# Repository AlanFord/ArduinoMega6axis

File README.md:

# ArduinoMega6axis
A stepper motor control shield for an Arduino Mega that will support 3 primary off-board motor controllers and 3 on-board Pololu A4988 controllers.  This supports work done at Build,RVA (http://rvabuild.com) to construct a Robot Arm (see http://fablab.ruc.dk/robot-arm-v-0-1/ ).

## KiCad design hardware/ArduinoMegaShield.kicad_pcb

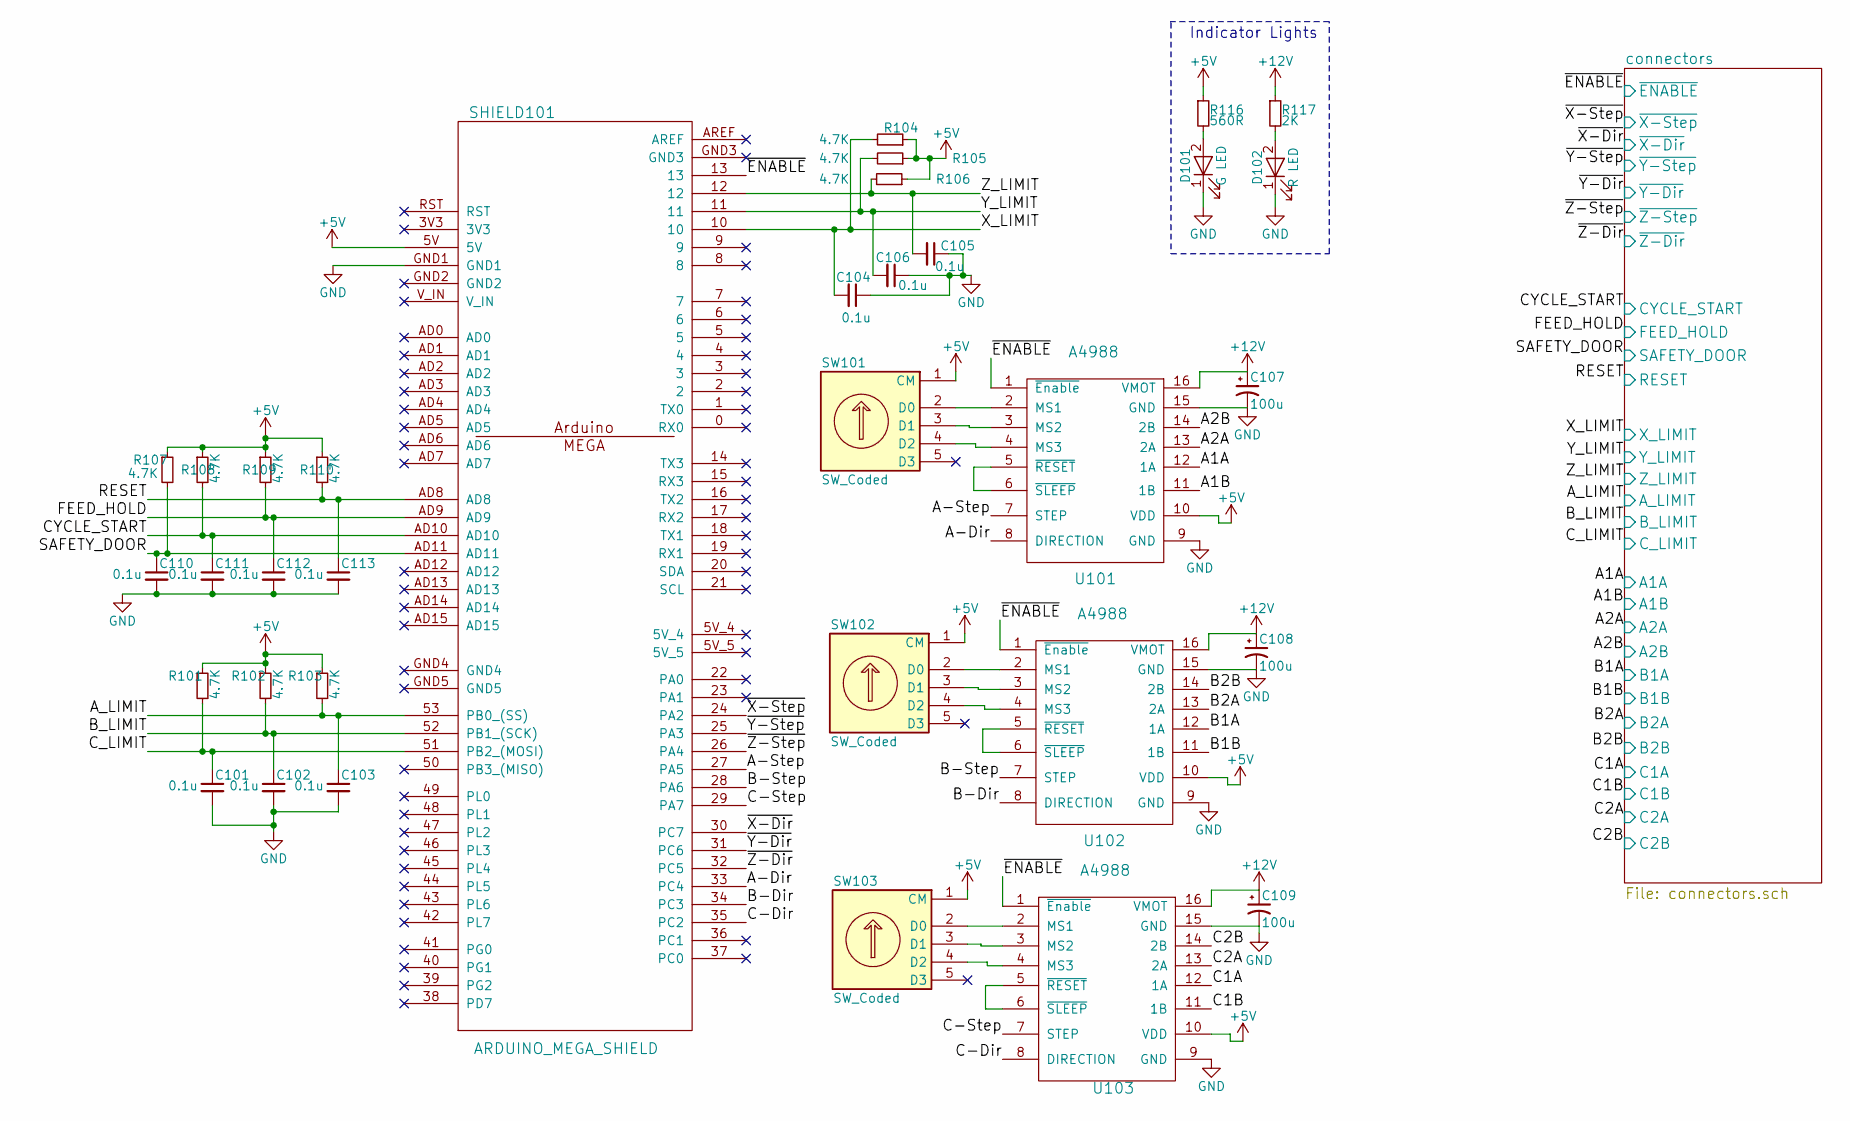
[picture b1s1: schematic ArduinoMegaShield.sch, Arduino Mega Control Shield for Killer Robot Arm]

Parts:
C101, C102, C103, C104, C105, C106, C110, C111, C112, C113: 0.1u; C_0805_HandSoldering
C107, C108, C109: 100u; C_Radial_D6.3_L11.2_P2.5; MPN EEU-FM1E101
D101: G LED; LED_0805
D102: R LED; LED_0805
R101, R102, R103, R104, R105, R106, R107, R108, R109, R110: 4.7K; R_0805_HandSoldering
R116: 560R; R_0805_HandSoldering
R117: 2K; R_0805_HandSoldering
SHIELD101: ARDUINO_MEGA_SHIELD
SW101, SW102, SW103: SW_Coded; S-1010A; MPN Copal S-1010A
U101, U102, U103: A4988

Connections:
+5V: R101.1, R102.1, R103.1, R104.1, R105.1, R106.1, R107.1, R108.1, R109.1, R110.1, R116.1, SHIELD101.5V, SW101.1 (CM), SW102.1 (CM), SW103.1 (CM), U101.10 (VDD), U102.10 (VDD), U103.10 (VDD); also elsewhere on the board
+12V: C107.1, C108.1, C109.1, R117.1, U101.16 (VMOT), U102.16 (VMOT), U103.16 (VMOT); also elsewhere on the board
/A1A: U101.12 (1A); also elsewhere on the board
/A1B: U101.11 (1B); also elsewhere on the board
/A2A: U101.13 (2A); also elsewhere on the board
/A2B: U101.14 (2B); also elsewhere on the board
/A-Dir: SHIELD101.33 (PC4), U101.8 (DIRECTION)
/A-Step: SHIELD101.27 (PA5), U101.7 (STEP)
/A_LIMIT: C103.1, R103.2, SHIELD101.53 (PB0_(SS)); also elsewhere on the board
/B1A: U102.12 (1A); also elsewhere on the board
/B1B: U102.11 (1B); also elsewhere on the board
/B2A: U102.13 (2A); also elsewhere on the board
/B2B: U102.14 (2B); also elsewhere on the board
/B-Dir: SHIELD101.34 (PC3), U102.8 (DIRECTION)
/B-Step: SHIELD101.28 (PA6), U102.7 (STEP)
/B_LIMIT: C102.1, R102.2, SHIELD101.52 (PB1_(SCK)); also elsewhere on the board
/C1A: U103.12 (1A); also elsewhere on the board
/C1B: U103.11 (1B); also elsewhere on the board
/C2A: U103.13 (2A); also elsewhere on the board
/C2B: U103.14 (2B); also elsewhere on the board
/C-Dir: SHIELD101.35 (PC2), U103.8 (DIRECTION)
/C-Step: SHIELD101.29 (PA7), U103.7 (STEP)
/CYCLE_START: C111.1, R108.2, SHIELD101.AD10; also elsewhere on the board
/C_LIMIT: C101.1, R101.2, SHIELD101.51 (PB2_(MOSI)); also elsewhere on the board
/FEED_HOLD: C112.1, R109.2, SHIELD101.AD9; also elsewhere on the board
/RESET: C113.1, R110.2, SHIELD101.AD8; also elsewhere on the board
/SAFETY_DOOR: C110.1, R107.2, SHIELD101.AD11; also elsewhere on the board
/X_LIMIT: C104.2, R104.2, SHIELD101.10; also elsewhere on the board
/Y_LIMIT: C106.2, R105.2, SHIELD101.11; also elsewhere on the board
/Z_LIMIT: C105.2, R106.2, SHIELD101.12; also elsewhere on the board
/~ENABLE: SHIELD101.13, U101.1 (~Enable), U102.1 (~Enable), U103.1 (~Enable); also elsewhere on the board
/~X-Dir: SHIELD101.30 (PC7); also elsewhere on the board
/~X-Step: SHIELD101.24 (PA2); also elsewhere on the board
/~Y-Dir: SHIELD101.31 (PC6); also elsewhere on the board
/~Y-Step: SHIELD101.25 (PA3); also elsewhere on the board
/~Z-Dir: SHIELD101.32 (PC5); also elsewhere on the board
/~Z-Step: SHIELD101.26 (PA4); also elsewhere on the board
GND: C101.2, C102.2, C103.2, C104.1, C105.1, C106.1, C107.2, C108.2, C109.2, C110.2, C111.2, C112.2, C113.2, D101.1 (K), D102.1 (K), SHIELD101.GND1, U101.9 (GND), U101.15 (GND), U102.9 (GND), U102.15 (GND), U103.9 (GND), U103.15 (GND); also elsewhere on the board
unnamed: D101.2 (A), R116.2
unnamed: D102.2 (A), R117.2
unnamed: SW101.2 (D0), U101.2 (MS1)
unnamed: SW101.3 (D1), U101.3 (MS2)
unnamed: SW101.4 (D2), U101.4 (MS3)
unnamed: SW102.2 (D0), U102.2 (MS1)
unnamed: SW102.3 (D1), U102.3 (MS2)
unnamed: SW102.4 (D2), U102.4 (MS3)
unnamed: SW103.2 (D0), U103.2 (MS1)
unnamed: SW103.3 (D1), U103.3 (MS2)
unnamed: SW103.4 (D2), U103.4 (MS3)
unnamed: U101.5 (~RESET), U101.6 (~SLEEP)
unnamed: U102.5 (~RESET), U102.6 (~SLEEP)
unnamed: U103.5 (~RESET), U103.6 (~SLEEP)

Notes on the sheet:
Indicator Lights

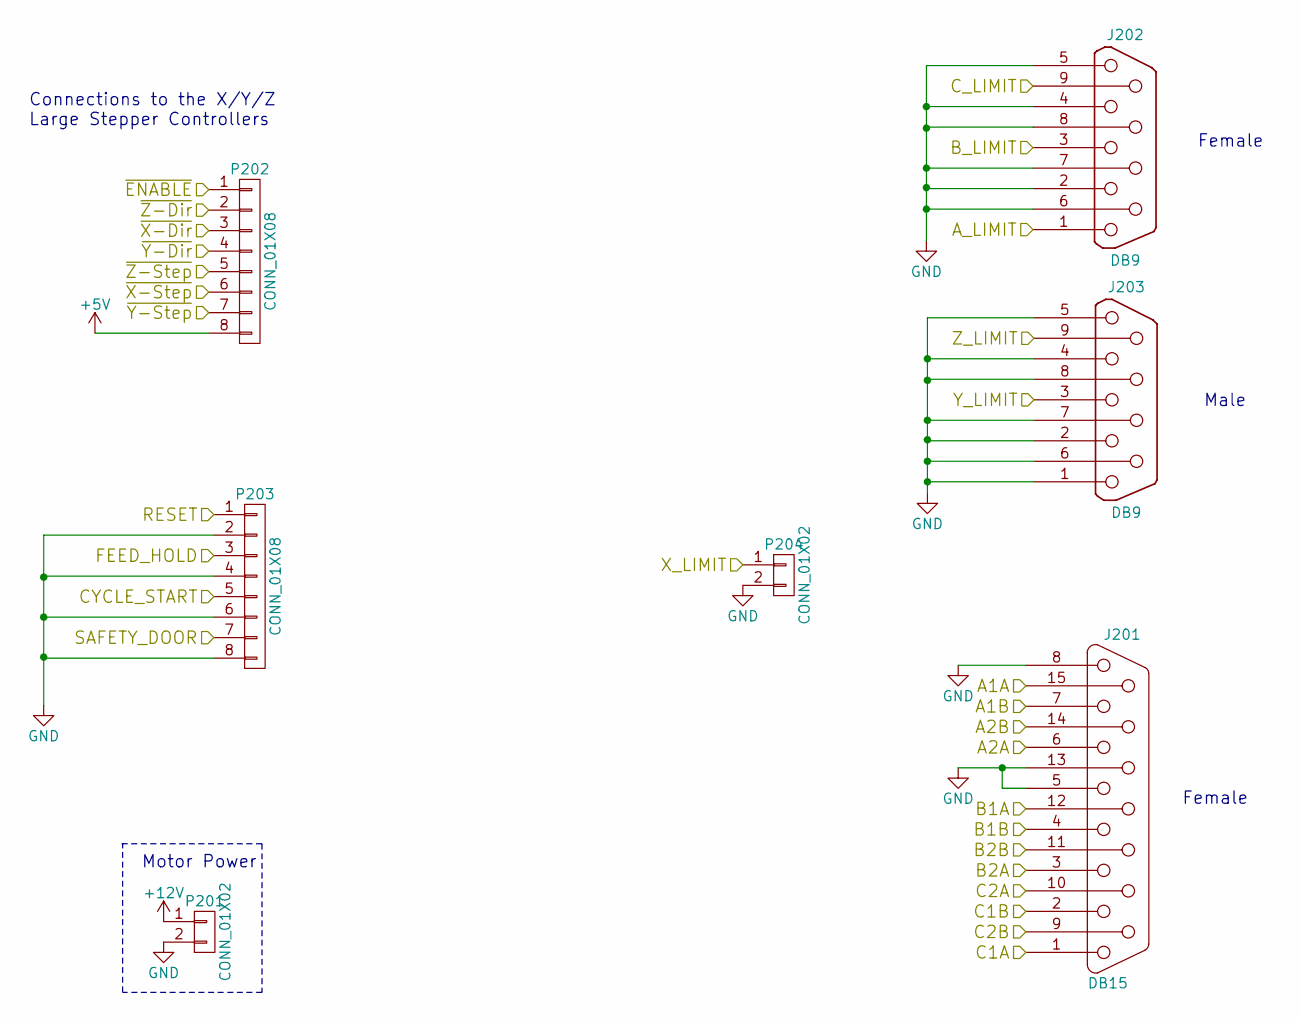
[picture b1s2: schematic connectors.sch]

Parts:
J201: DB15; D15S33E4GV00LF; MPN D15S33E4GV00LF
J202: DB9; LD09S33E4GV00LF; MPN LD09S33E4GV00LF
J203: DB9; LD09P33E4GV00LF; MPN LD09P33E4GV00LF
P201, P204: CONN_01X02; Terminal_Block_200_mil; MPN OSTTC022162
P202, P203: CONN_01X08; Terminal_Block_200_mil_8pos; MPN OSTTC022162

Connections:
+5V: P202.8; also elsewhere on the board
+12V: P201.1; also elsewhere on the board
/A1A: J201.15; also elsewhere on the board
/A1B: J201.7; also elsewhere on the board
/A2A: J201.6; also elsewhere on the board
/A2B: J201.14; also elsewhere on the board
/A_LIMIT: J202.1; also elsewhere on the board
/B1A: J201.12; also elsewhere on the board
/B1B: J201.4; also elsewhere on the board
/B2A: J201.3; also elsewhere on the board
/B2B: J201.11 (P111); also elsewhere on the board
/B_LIMIT: J202.3; also elsewhere on the board
/C1A: J201.1; also elsewhere on the board
/C1B: J201.2; also elsewhere on the board
/C2A: J201.10; also elsewhere on the board
/C2B: J201.9; also elsewhere on the board
/CYCLE_START: P203.5; also elsewhere on the board
/C_LIMIT: J202.9; also elsewhere on the board
/FEED_HOLD: P203.3; also elsewhere on the board
/RESET: P203.1; also elsewhere on the board
/SAFETY_DOOR: P203.7; also elsewhere on the board
/X_LIMIT: P204.1; also elsewhere on the board
/Y_LIMIT: J203.3; also elsewhere on the board
/Z_LIMIT: J203.9; also elsewhere on the board
/~ENABLE: P202.1; also elsewhere on the board
/~X-Dir: P202.3; also elsewhere on the board
/~X-Step: P202.6; also elsewhere on the board
/~Y-Dir: P202.4; also elsewhere on the board
/~Y-Step: P202.7; also elsewhere on the board
/~Z-Dir: P202.2; also elsewhere on the board
/~Z-Step: P202.5; also elsewhere on the board
GND: J201.5, J201.8, J201.13, J202.2, J202.4, J202.5, J202.6, J202.7, J202.8, J203.1, J203.2, J203.4, J203.5, J203.6, J203.7, J203.8, P201.2, P203.2, P203.4, P203.6, P203.8, P204.2; also elsewhere on the board

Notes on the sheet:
Motor Power
Connections to the X/Y/Z Large Stepper Controllers
Female
Male

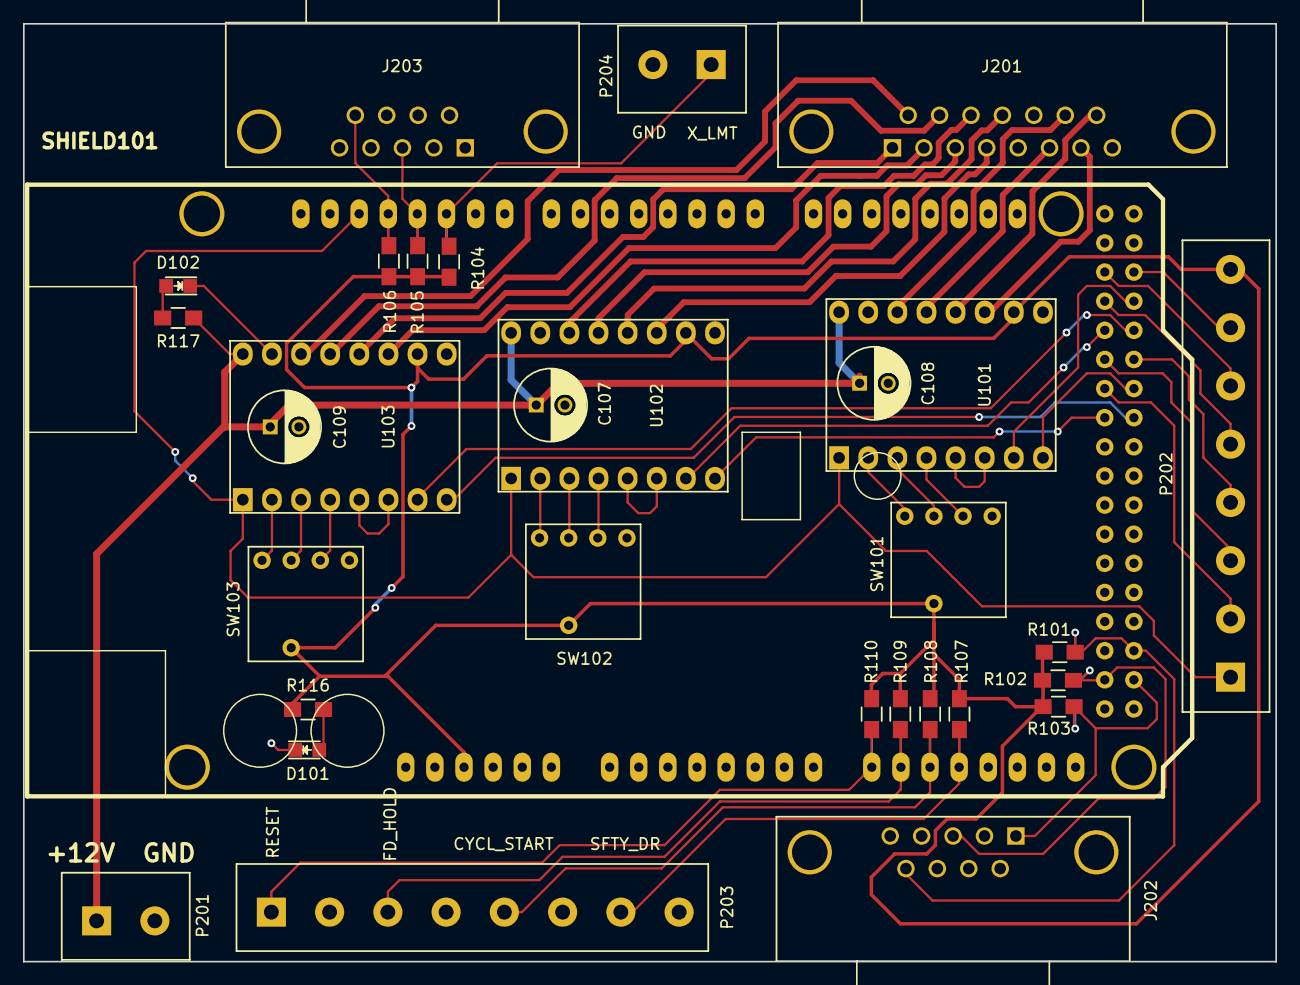
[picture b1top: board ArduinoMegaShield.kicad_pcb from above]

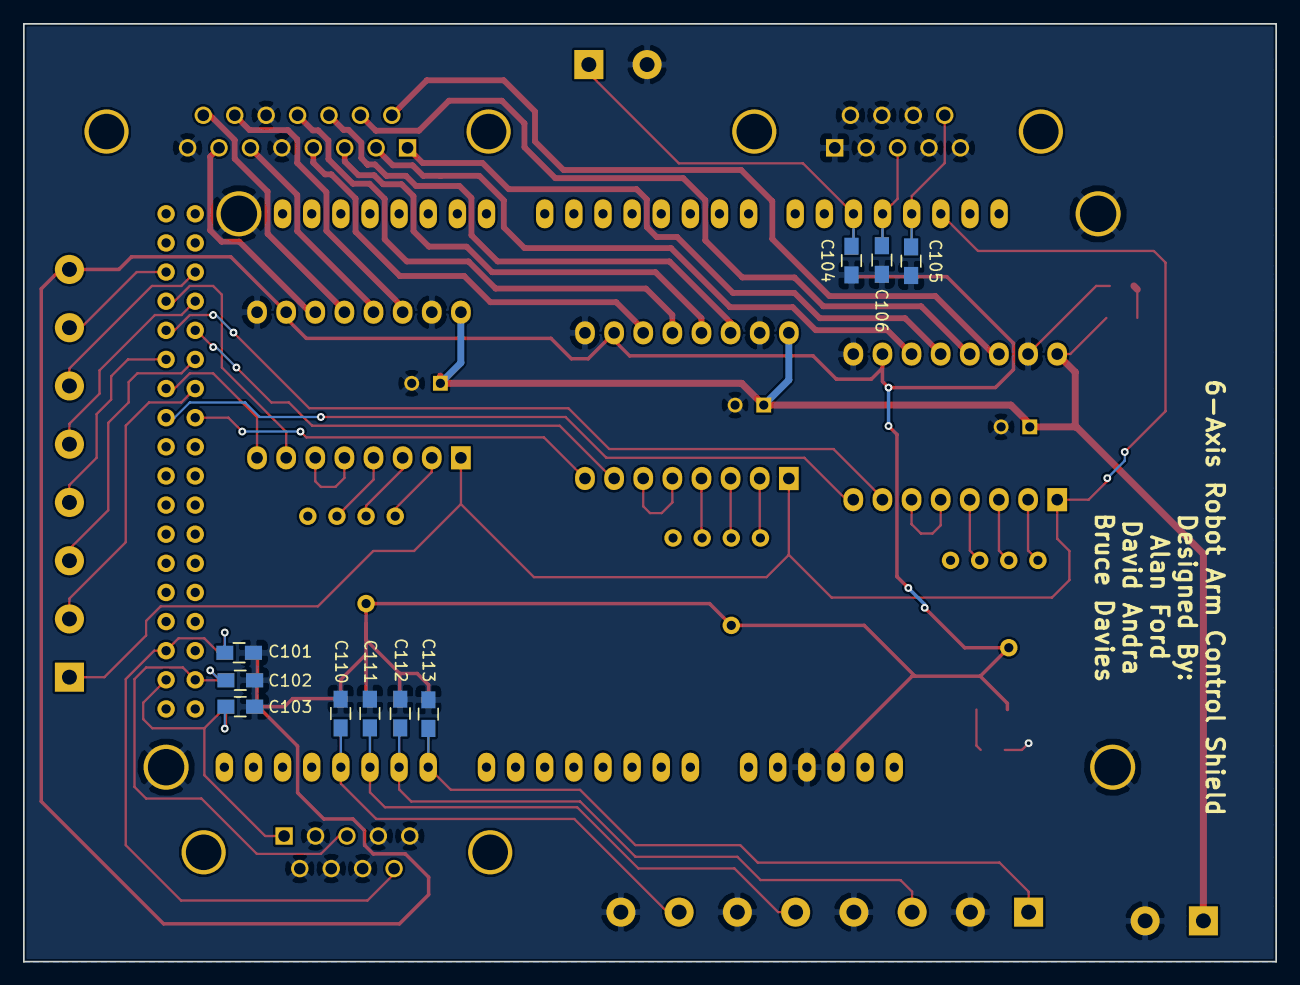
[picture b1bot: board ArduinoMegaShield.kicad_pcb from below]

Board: 2 copper layers, 109.2 x 81.8 mm, 41 parts (10 on the bottom side), 52 nets.

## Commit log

2017-07-21 initial cut at schematic
2017-07-21 generated a pdf of the schematic
2017-07-22 added microstepping NOPOP resistors and power indicator LEDs. Assigned some footprints
2017-07-22 updated schematic pdf
2017-07-22 correctly logic of steps/dir on shield output pins
2017-07-22 initiated pcb layout
2017-07-22 changed terminal connectors from dupont to 200 mil screw terminals
2017-07-22 added footprints for caps and motor drivers
2017-07-22 added terminal connections for limit switches
2017-07-22 added note about limit switches being on a single bank/port
2017-07-23 added NOPOPs for optional pullups on limit switches
2017-07-31 added caps to the limit switches
2017-08-02 added estop on the avr reset pin
2017-08-02 added safety-door switch as a halt-but-don't-downpower option
2017-08-07 changed pull down resistor to 4.7k and added note about rotary dip switch
2017-08-09 wired ~SLEEP and ~RESET together on small stepper drivers
2017-08-20 added switches for cycle_start and feed_hold, added docs for protoboard mockup
2017-08-23 moved connectors to separate sheet and started board layout
2017-08-25 changed connector footprints and added rotory dip switch footprint
2017-08-29 changed dsub connectors to horizontal
2017-08-30 completed board and generated gerbers
2017-09-09 added photos, layouts, and instructions for Rev. 0
